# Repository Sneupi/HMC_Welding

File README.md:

# Description

Repo for HMC welding project.

Code is arranged into three files (1 for each device). Arranged as a PlatformIO project for any Pro Mini or UNO (ATMega328P) boards. File `src/main.cpp` indicates which device is to-be-flashed.

Breakout PCBs are located in `kicad`, made with KiCad (8.0) software.

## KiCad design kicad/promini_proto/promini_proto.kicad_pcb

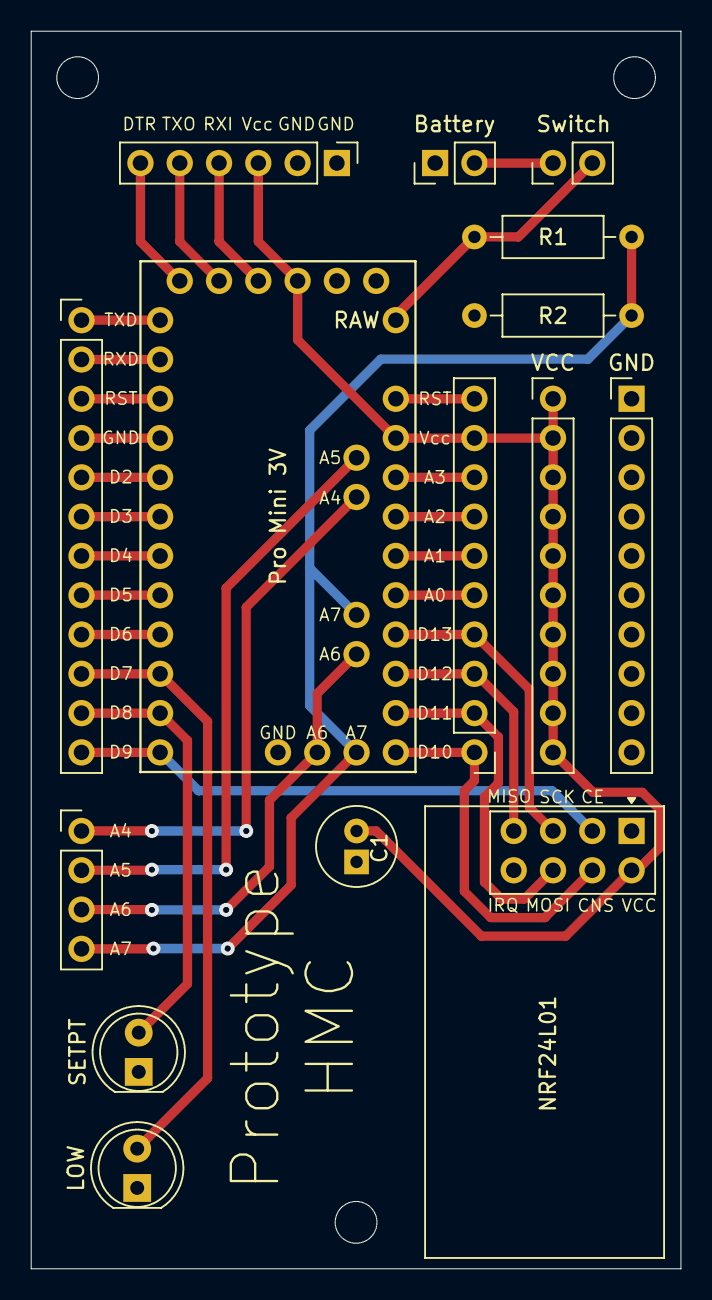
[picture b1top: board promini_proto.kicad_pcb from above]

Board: 4 copper layers, 42.0 x 80.0 mm, 15 parts (0 on the bottom side), 31 nets.

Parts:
Battery: Conn_01x02; PinHeader_1x02_P2.54mm_Vertical
C1: C_Polarized; C_Radial_D5.0mm_H11.0mm_P2.00mm
FTDI1: Conn_01x06; PinHeader_1x06_P2.54mm_Vertical
GND: Conn_01x10; PinHeader_1x10_P2.54mm_Vertical
JBottom1: Conn_01x04; PinHeader_1x04_P2.54mm_Vertical
JLeft1: Conn_01x12; PinHeader_1x12_P2.54mm_Vertical
JRight1: Conn_01x10; PinHeader_1x10_P2.54mm_Vertical
LOW: LED; LED_D5.0mm
NRF24L01: NRF24L01_Breakout; nRF24L01_Breakout
Pro Mini 3V: Pro_Mini; Pro_Mini_Universal
R1, R2: R; R_Axial_DIN0207_L6.3mm_D2.5mm_P10.16mm_Horizontal
SETPT: LED; LED_D5.0mm
Switch: Conn_01x02; PinHeader_1x02_P2.54mm_Vertical
VCC: Conn_01x10; PinHeader_1x10_P2.54mm_Vertical

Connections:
A0: JRight1.5, Pro Mini 3V.26 (PC0/A0)
A1: JRight1.6, Pro Mini 3V.25 (PC1/A1)
A2: JRight1.7, Pro Mini 3V.24 (PC2/A2)
A3: JRight1.8, Pro Mini 3V.23 (PC3/A3)
A4: JBottom1.1, Pro Mini 3V.31 (PA4)
A5: JBottom1.2, Pro Mini 3V.32 (PA5)
A6: JBottom1.3, Pro Mini 3V.33 (PA6)
A7: JBottom1.4, Pro Mini 3V.34 (PA7), R1.2, R2.1
D2: JLeft1.5, Pro Mini 3V.11 (PD2)
D3: JLeft1.6, Pro Mini 3V.12 (PD3)
D4: JLeft1.7, Pro Mini 3V.13 (PD4)
D5: JLeft1.8, Pro Mini 3V.14 (PD5)
D6: JLeft1.9, Pro Mini 3V.15 (PD6)
D7: JLeft1.10, LOW.2 (A), Pro Mini 3V.16 (PD7)
D8: JLeft1.11, Pro Mini 3V.17 (PB0), SETPT.2 (A)
D9: JLeft1.12, NRF24L01.3 (CE), Pro Mini 3V.18 (PB1)
D10: JRight1.1, NRF24L01.4 (~CSN), Pro Mini 3V.30 (PB2)
DTR: FTDI1.6, Pro Mini 3V.6 (DTR-CBL)
GND: Battery.1, C1.2, FTDI1.1, FTDI1.2, GND.1, GND.2, GND.3, GND.4, GND.5, GND.6, GND.7, GND.8, GND.9, GND.10, JLeft1.4, LOW.1 (K), NRF24L01.1 (GND), Pro Mini 3V.1 (GND), Pro Mini 3V.2 (GND), Pro Mini 3V.10 (GND), R2.2, SETPT.1 (K)
MISO: JRight1.3, NRF24L01.7 (MISO), Pro Mini 3V.28 (PB4)
MOSI: JRight1.2, NRF24L01.6 (MOSI), Pro Mini 3V.29 (PB3)
unnamed: Battery.2, Switch.1
RAW: Pro Mini 3V.19 (RAW), R1.1, Switch.2
RST: JRight1.10, Pro Mini 3V.21 (RESET)
RST1: JLeft1.3, Pro Mini 3V.9 (RESET)
RX1: FTDI1.4, Pro Mini 3V.4 (RX1-CBL)
RX_D1: JLeft1.2, Pro Mini 3V.8 (RX_D0)
SCK: JRight1.4, NRF24L01.5 (SCK), Pro Mini 3V.27 (PB5)
TX0: FTDI1.5, Pro Mini 3V.5 (TX0-CBL)
TX_D0: JLeft1.1, Pro Mini 3V.7 (TX0_D1)
Vcc: C1.1, FTDI1.3, JRight1.9, NRF24L01.2 (VCC), Pro Mini 3V.3 (Vcc-CBL), Pro Mini 3V.22 (Vcc), VCC.1, VCC.2, VCC.3, VCC.4, VCC.5, VCC.6, VCC.7, VCC.8, VCC.9, VCC.10

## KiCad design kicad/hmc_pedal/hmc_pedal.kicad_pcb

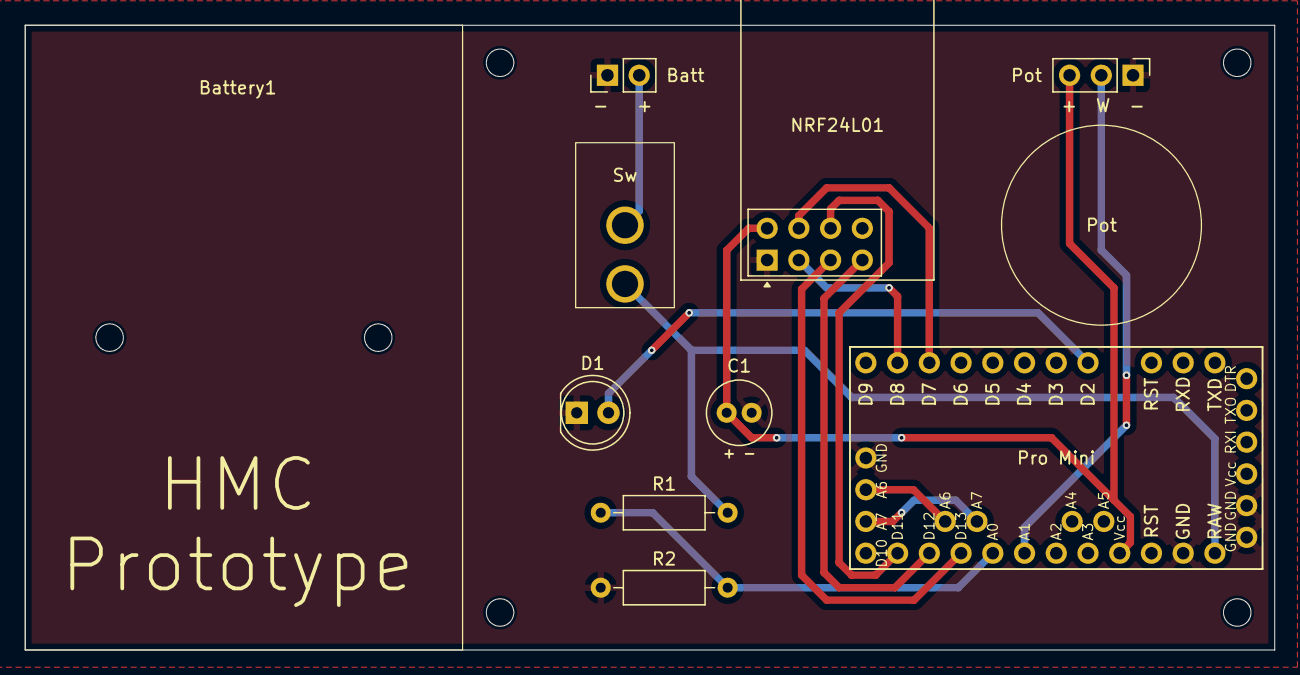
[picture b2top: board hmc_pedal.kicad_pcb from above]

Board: 4 copper layers, 100.0 x 50.0 mm, 9 parts (0 on the bottom side), 12 nets.

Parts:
Battery1: Conn_01x02; PinHeader_1x02_P2.54mm_Vertical
C1: C_Polarized; C_Radial_D5.0mm_H11.0mm_P2.00mm
D1: LED; LED_D5.0mm
NRF24L01: NRF24L01_Breakout; nRF24L01_Breakout
Pot: Conn_01x03; PinHeader_1x03_P2.54mm_Vertical
Pro Mini: Pro_Mini; Pro_Mini_Universal
R1, R2: R; R_Axial_DIN0207_L6.3mm_D2.5mm_P10.16mm_Horizontal
Sw: SW_SPST; SW_SPSTx01_Taiss

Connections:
A_BATT: Pro Mini.26 (PC0/A0), R1.2, R2.1
A_POT: Pot.2, Pro Mini.25 (PC1/A1)
CE: NRF24L01.3 (CE), Pro Mini.17 (PB0)
CSN: NRF24L01.4 (~CSN), Pro Mini.16 (PD7)
D_BATT: D1.2 (A), Pro Mini.11 (PD2)
GND: Battery1.1, C1.2, D1.1 (K), NRF24L01.1 (GND), Pot.1, Pro Mini.1 (GND), Pro Mini.2 (GND), Pro Mini.10 (GND), Pro Mini.20 (GND), R2.2
MISO: NRF24L01.7 (MISO), Pro Mini.28 (PB4)
MOSI: NRF24L01.6 (MOSI), Pro Mini.29 (PB3)
RAW: Pro Mini.19 (RAW), R1.1, Sw.2 (B)
SCK: NRF24L01.5 (SCK), Pro Mini.27 (PB5)
SW: Battery1.2, Sw.1 (A)
VCC: C1.1, NRF24L01.2 (VCC), Pot.3, Pro Mini.22 (Vcc)

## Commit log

2024-12-17 base
2024-12-18 simple rxtx
2024-12-30 tx #defines
2024-12-30 change pot default
2024-12-31 add servo lib
2024-12-31 rx relay & servo code
2025-01-01 update tx pins
2025-01-01 5v mini config
2025-01-03 2nd rf address
2025-01-03 proto controller code
2025-01-03 update device select
2025-01-28 kicad pcb files
